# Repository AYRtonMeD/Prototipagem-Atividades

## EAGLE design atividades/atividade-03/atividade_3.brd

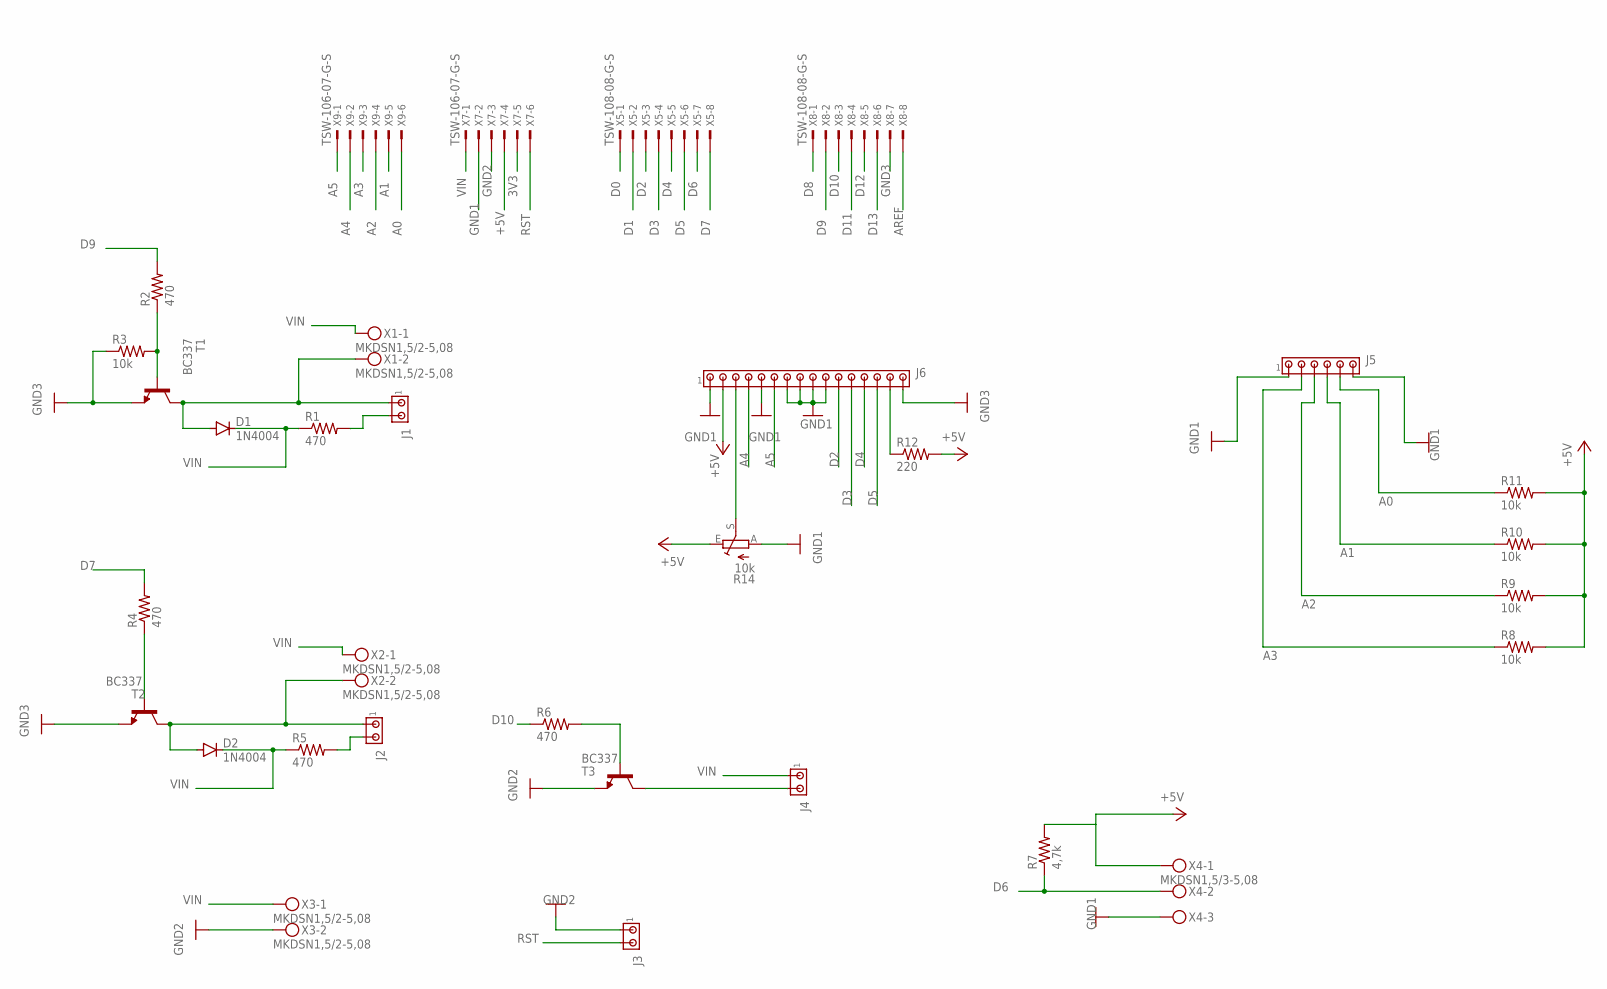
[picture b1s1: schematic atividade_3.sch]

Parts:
D1, D2: 1N4004; DO41-10
J1, J2, J3, J4: MTA02-100; 10X02MTA
J5: MTA06-100; 10X06MTA
J6: MTA16-156; 1X16MTA
R1, R2, R4, R5, R6: 470; 0204/7
R3, R8, R9, R10, R11: 10k; 0204/7
R7: 4,7k; 0204/7
R12: 220; 0204/7
R14: 10k; CA6H
T1, T2, T3: BC337; TO92
X1, X2, X3: MKDSN1,5/2-5,08
X4: MKDSN1,5/3-5,08
X5, X8: TSW-108-08-G-S; TSW-108-XX-G-S
X7, X9: TSW-106-07-G-S; TSW-106-XX-G-S

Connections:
3V3: X7.5
+5V: J6.2, R7.2, R8.2, R9.2, R10.2, R11.2, R12.2, R14.E, X4.1, X7.4
A0: J5.5, R11.1, X9.6
A1: J5.4, R10.1, X9.5
A2: J5.3, R9.1, X9.4
A3: J5.2, R8.1, X9.3
A4: J6.4, X9.2
A5: J6.6, X9.1
AREF: X8.8
D0: X5.1
D1: X5.2
D2: J6.11, X5.3
D3: J6.12, X5.4
D4: J6.13, X5.5
D5: J6.14, X5.6
D6: R7.1, X4.2, X5.7
D7: R4.2, X5.8
D8: X8.1
D9: R2.2, X8.2
D10: R6.1, X8.3
D11: X8.4
D12: X8.5
D13: X8.6
GND1: J5.1, J5.6, J6.1, J6.5, J6.7, J6.8, J6.9, J6.10, R14.A, X4.3, X7.2
GND2: J3.1, T3.1 (E), X3.2, X7.3
GND3: J6.16, R3.1, T1.1 (E), T2.1 (E), X8.7
unnamed: D1.A, J1.1, T1.3 (C), X1.2
unnamed: D2.A, J2.1, T2.3 (C), X2.2
unnamed: J1.2, R1.2
unnamed: J2.2, R5.2
unnamed: R2.1, R3.2, T1.2 (B)
unnamed: R4.1, T2.2 (B)
unnamed: R6.2, T3.2 (B)
unnamed: J4.2, T3.3 (C)
unnamed: J6.3, R14.S
unnamed: J6.15, R12.1
RST: J3.2, X7.6
VIN: D1.C, D2.C, J4.1, R1.1, R5.1, X1.1, X2.1, X3.1, X7.1

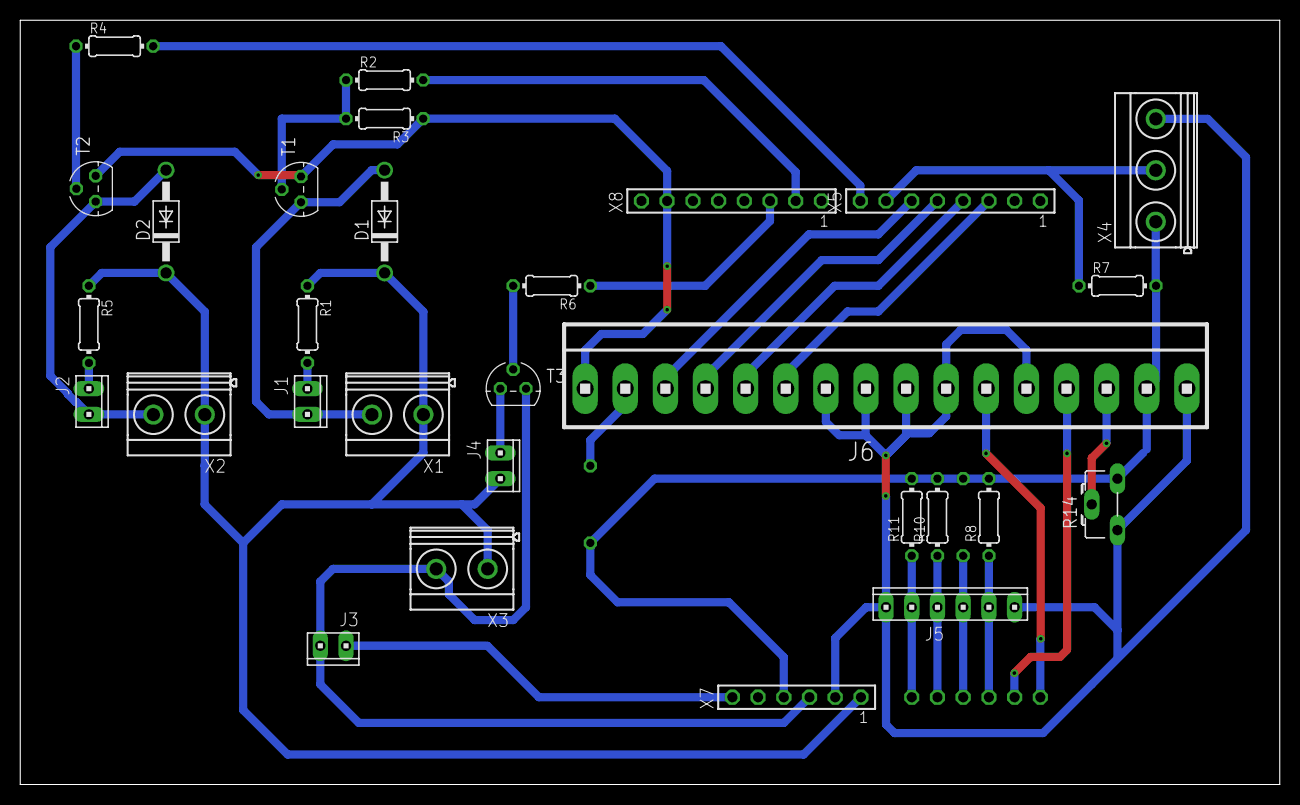
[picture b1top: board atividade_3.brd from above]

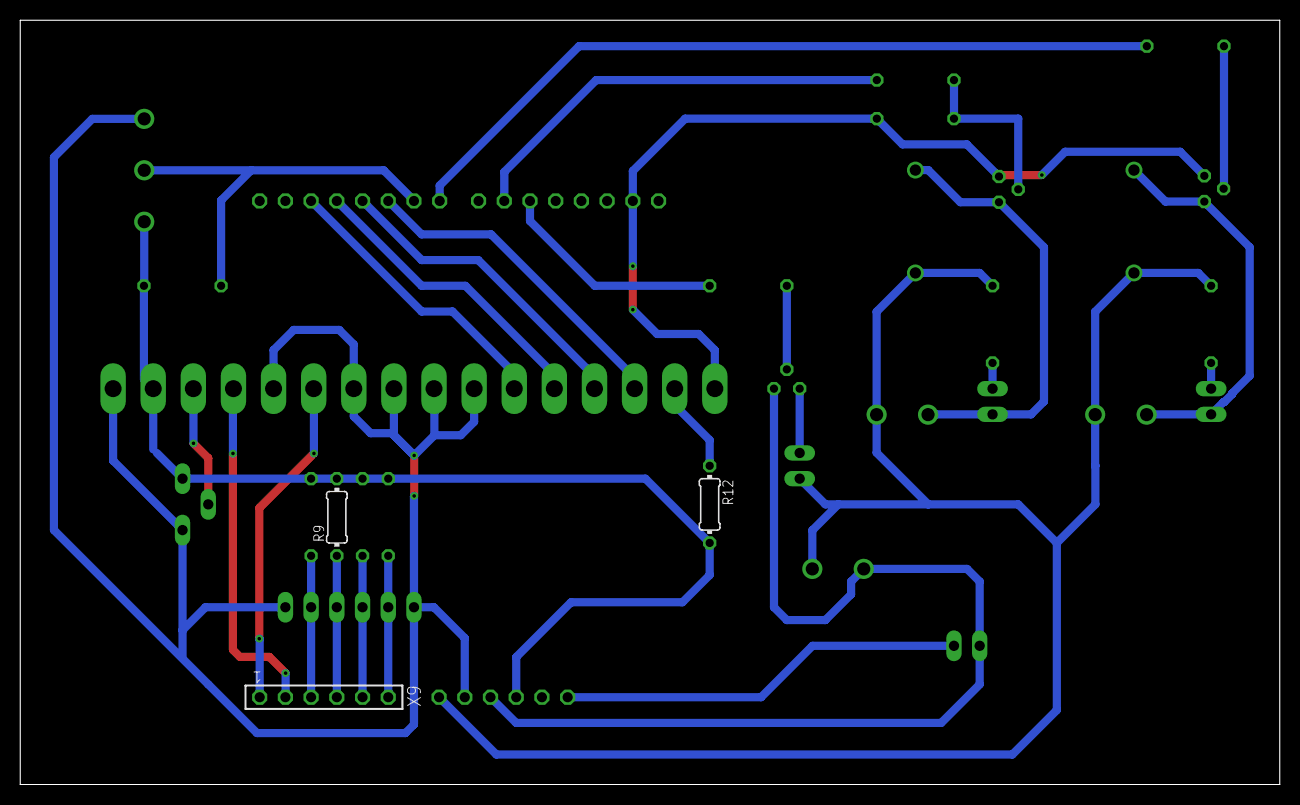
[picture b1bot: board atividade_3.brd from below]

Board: 2 copper layers, 124.4 x 75.5 mm, 32 parts (3 on the bottom side), 30 nets.

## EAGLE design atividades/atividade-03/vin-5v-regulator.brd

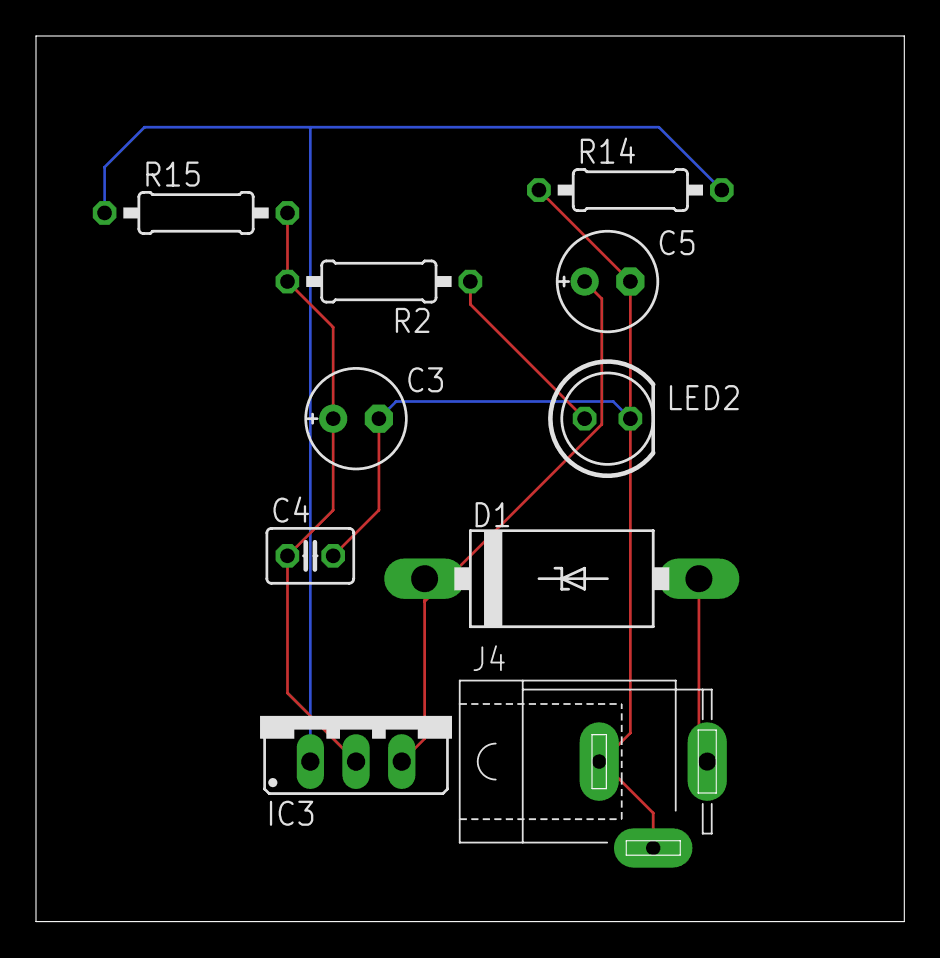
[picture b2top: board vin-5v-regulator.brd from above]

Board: 2 copper layers, 48.2 x 49.2 mm, 10 parts (0 on the bottom side), 6 nets.

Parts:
C3: 10uF; E2,5-6E
C4: 100nF; C025-030X050
C5: 47uF; E2,5-6E
D1: 1N5908; C4111-15
IC3: LM317; 317TS
J4: SPC4077
LED2: VERDE; LED5MM
R2: 1K; 0207/10
R14: 715; 0207/10
R15: 240; 0207/10

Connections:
+5V: C3.+, C4.1, IC3.2, R2.2, R15.2
GND: C3.-, C4.2, C5.-, J4.1, J4.2, LED2.K, R14.1
unnamed: D1.A, J4.3
unnamed: C5.+, D1.C, IC3.3
unnamed: IC3.1, R14.2, R15.1
unnamed: LED2.A, R2.1

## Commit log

2021-12-06 Atividade 2 da disciplina de tecnicas de prototipagem!
2021-12-14 Atividade 3 da disciplina de tecnicas de prototipagem!
2021-12-29 Atividade 4 da disciplina de tecnicas de prototipagem!
